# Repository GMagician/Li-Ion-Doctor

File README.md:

# Lithium battery doctor

**PROOF OF CONCEPT PROJECT**

**:warning::boom: WARNING:LITHIUM BATTERY MAY EASILY EXPLODE OR TAKE FIRE, REPLICATE THIS PROJECT AT YOUR OWN RISK:boom::warning:**

Complete solution for Li Ion batteries

Features:<br />
  Charge, discharge, amp hours count, test for short or open circuit, weak battery indicator, measure internal resistance.

- Charge:<br />
  TP4056 module (integrated), selectable current ~200/500/1000mA. TP4056 circuit is monitored by Arduino.
- Discharge:<br />
  current up to 2000mA (step 20mA), PWM controlled. Internal resistance is calculated from battery voltage drop under load.
- Capacity:<br />
  Battery gets fully charged, then discharged, mAh on selected current load is counted.
- Recovery:<br />
  Deep discharged battery charge with 100mA current.<br /><br />

This is a revisited project originally developped by Akos Boda in 2022 (https://www.thingiverse.com/thing:5229303).

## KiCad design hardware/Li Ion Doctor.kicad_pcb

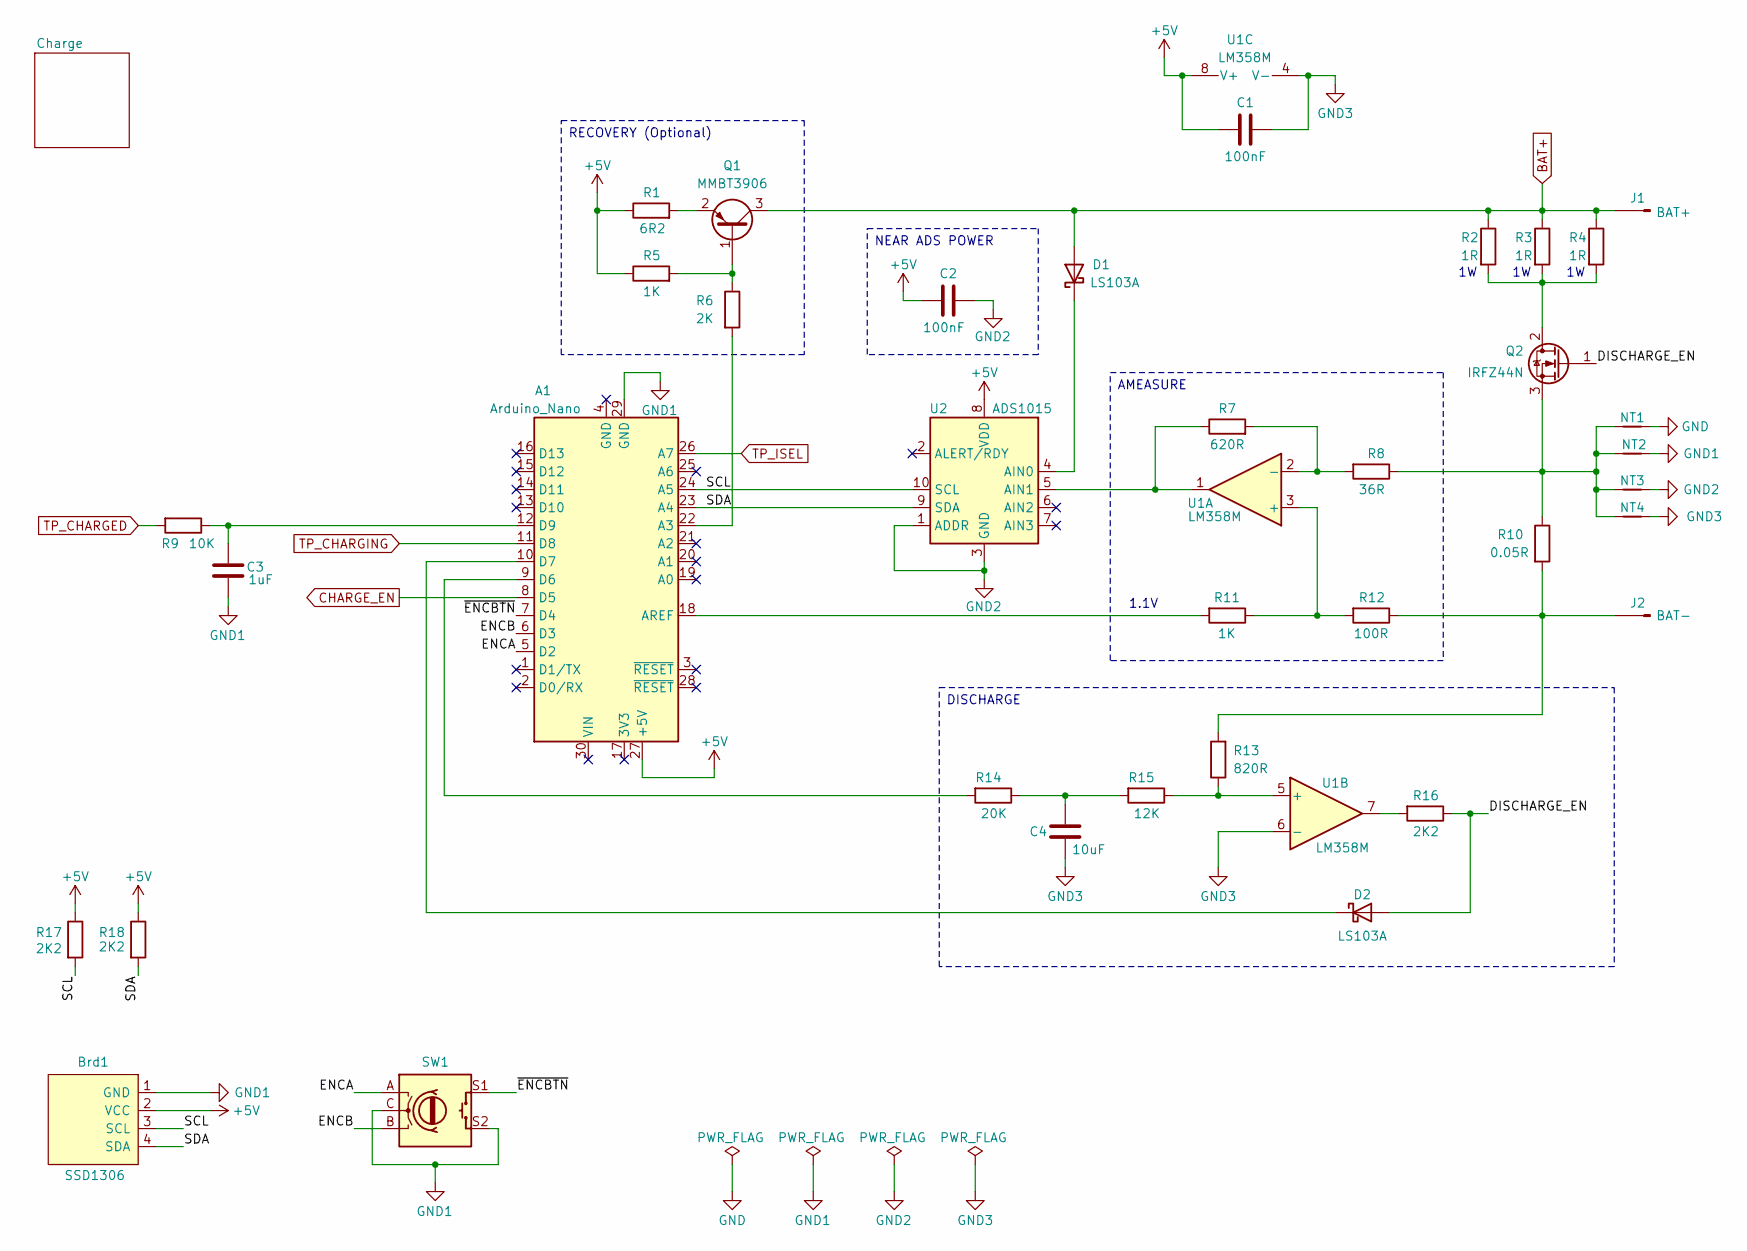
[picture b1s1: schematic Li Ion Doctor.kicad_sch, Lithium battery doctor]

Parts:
A1: Arduino_Nano
Brd1: SSD1306; SSD1306_OLED_DISPLAY_0.96
C1, C2: 100nF; C_0805_2012Metric_Pad1.18x1.45mm_HandSolder
C3: 1uF; C_0805_2012Metric_Pad1.18x1.45mm_HandSolder
C4: 10uF; C_0805_2012Metric_Pad1.18x1.45mm_HandSolder
D1, D2: LS103A; D_SOD-80
J1: BAT+; Pin_D1.0mm_L10.0mm_LooseFit
J2: BAT-; Pin_D1.0mm_L10.0mm_LooseFit
NT1: NetTie_2; NetTie-2_SMD_Pad2.0mm
NT2, NT3, NT4: NetTie_2; NetTie-2_SMD_Pad0.5mm
Q1: MMBT3906; SOT-23
Q2: IRFZ44N; TO-220-3_Vertical
R1: 6R2; R_0805_2012Metric_Pad1.20x1.40mm_HandSolder
R2, R3, R4: 1R; R_2512_6332Metric_Pad1.40x3.35mm_HandSolder
R5, R11: 1K; R_0805_2012Metric_Pad1.20x1.40mm_HandSolder
R6: 2K; R_0805_2012Metric_Pad1.20x1.40mm_HandSolder
R7: 620R; R_0805_2012Metric_Pad1.20x1.40mm_HandSolder
R8: 36R; R_0805_2012Metric_Pad1.20x1.40mm_HandSolder
R9: 10K; R_0805_2012Metric_Pad1.20x1.40mm_HandSolder
R10: 0.05R; R_Bare_Metal_Element_L18mm_W2.5mm_P15mm
R12: 100R; R_0805_2012Metric_Pad1.20x1.40mm_HandSolder
R13: 820R; R_0805_2012Metric_Pad1.20x1.40mm_HandSolder
R14: 20K; R_0805_2012Metric_Pad1.20x1.40mm_HandSolder
R15: 12K; R_0805_2012Metric_Pad1.20x1.40mm_HandSolder
R16, R17, R18: 2K2; R_0805_2012Metric_Pad1.20x1.40mm_HandSolder
SW1: RotaryEncoder_Switch; RotaryEncoder-Switch_Vertical_H15mm
U1: LM358M; SOP-8_3.9x4.9mm_P1.27mm
U2: ADS1015; TSSOP-10_3x3mm_P0.5mm

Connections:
+5V: A1.27 (+5V), Brd1.2 (VCC), C1.1, C2.1, R1.1, R5.1, R17.1, R18.1, U1.8 (V+), U2.8 (VDD); also elsewhere on the board
/DISCHARGE_EN: D2.2 (A), Q2.1 (G), R16.1
/ENCA: A1.5 (D2), SW1.A
/ENCB: A1.6 (D3), SW1.B
/SCL: A1.24 (A5), Brd1.3 (SCL), R17.2, U2.10 (SCL)
/SDA: A1.23 (A4), Brd1.4 (SDA), R18.2, U2.9 (SDA)
/~ENCBTN: A1.7 (D4), SW1.S1
BAT+: D1.2 (A), J1.1, Q1.3 (C), R2.1, R3.1, R4.1; also elsewhere on the board
CHARGE_EN: A1.8 (D5); also elsewhere on the board
GND: NT1.1; also elsewhere on the board
GND1: A1.29 (GND), Brd1.1 (GND), C3.1, NT2.1, SW1.C, SW1.S2; also elsewhere on the board
GND2: C2.2, NT3.1, U2.1 (ADDR), U2.3 (GND)
GND3: C1.2, C4.2, NT4.1, U1.4 (V-), U1.6 (-)
unnamed: A1.22 (A3), R6.2
unnamed: A1.18 (AREF), R11.2
unnamed: A1.9 (D6), R14.2
unnamed: A1.10 (D7), D2.1 (K)
unnamed: A1.12 (D9), C3.2, R9.1
unnamed: C4.1, R14.1, R15.2
unnamed: D1.1 (K), U2.4 (AIN0)
unnamed: J2.1, R10.2, R12.1, R13.2
unnamed: Q1.1 (B), R5.2, R6.1
unnamed: Q1.2 (E), R1.2
unnamed: Q2.2 (D), R2.2, R3.2, R4.2
unnamed: NT1.2, NT2.2, NT3.2, NT4.2, Q2.3 (S), R8.1, R10.1
unnamed: R16.2, U1.7
unnamed: R11.1, R12.2, U1.3 (+)
unnamed: R7.2, R8.2, U1.2 (-)
unnamed: R13.1, R15.1, U1.5 (+)
unnamed: R7.1, U1.1, U2.5 (AIN1)
TP_CHARGED: R9.2; also elsewhere on the board
TP_CHARGING: A1.11 (D8); also elsewhere on the board
TP_ISEL: A1.26 (A7); also elsewhere on the board

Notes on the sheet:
1.1V
DISCHARGE
RECOVERY (Optional)
NEAR ADS POWER
AMEASURE

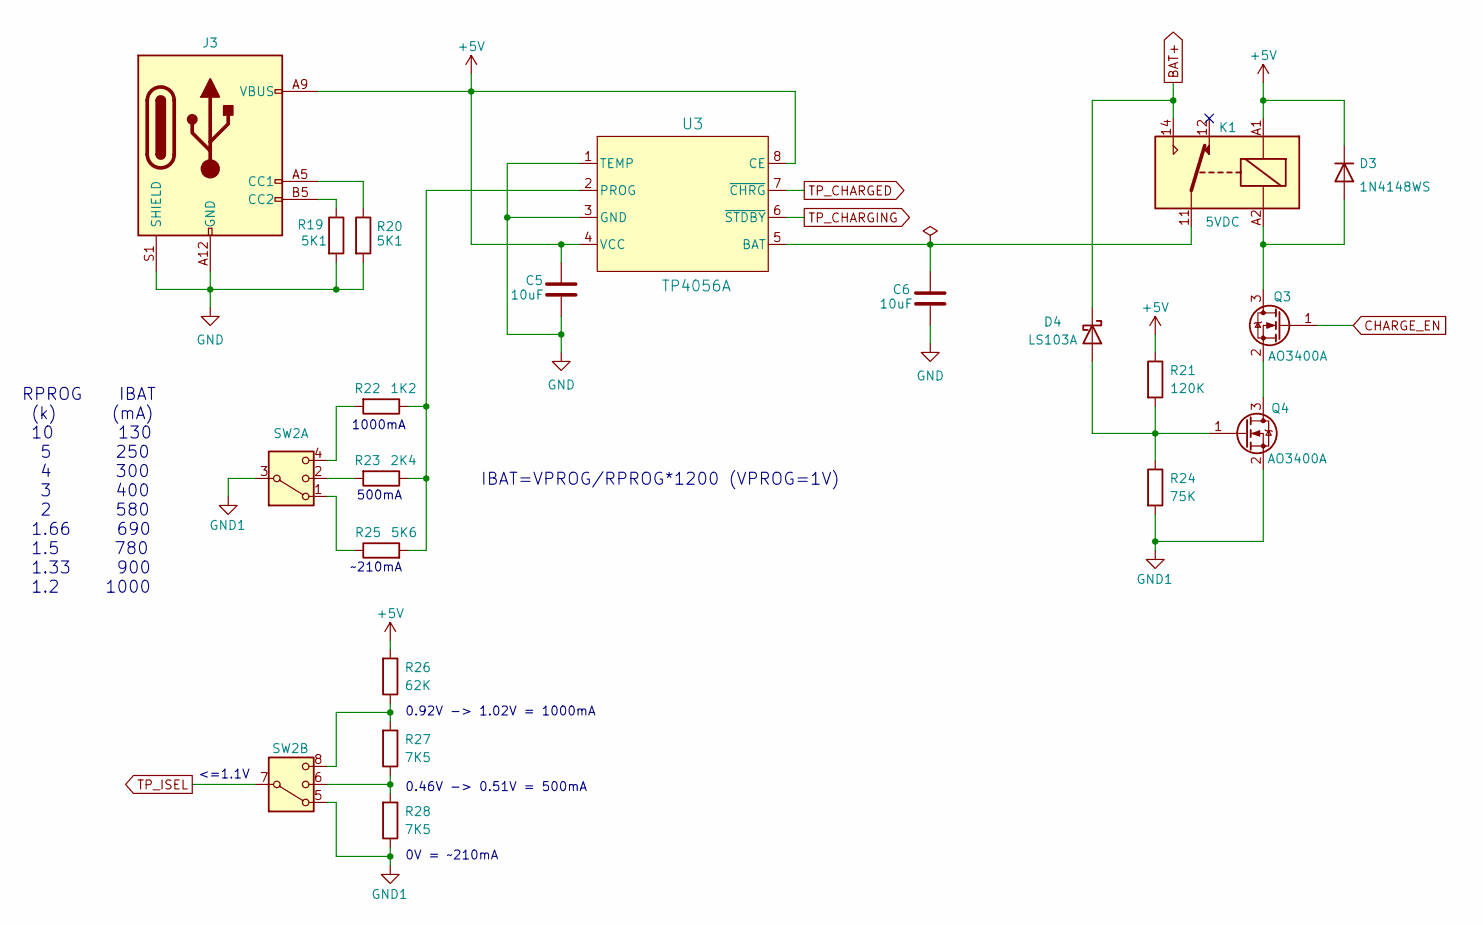
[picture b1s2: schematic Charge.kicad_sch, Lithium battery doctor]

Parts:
C5, C6: 10uF; C_0805_2012Metric_Pad1.18x1.45mm_HandSolder
D3: 1N4148WS; D_SOD-323_HandSoldering
D4: LS103A; D_SOD-80
J3: USB_C_Receptacle_PowerOnly_6P; USB_C_Receptacle_GCT_USB4125-xx-x_6P_TopMnt_Horizontal
K1: 5VDC; Relay_SPDT_Finder_36.11
Q3, Q4: AO3400A; SOT-23
R19, R20: 5K1; R_0805_2012Metric_Pad1.20x1.40mm_HandSolder
R21: 120K; R_0805_2012Metric_Pad1.20x1.40mm_HandSolder
R22: 1K2; R_0805_2012Metric_Pad1.20x1.40mm_HandSolder
R23: 2K4; R_0805_2012Metric_Pad1.20x1.40mm_HandSolder
R24: 75K; R_0805_2012Metric_Pad1.20x1.40mm_HandSolder
R25: 5K6; R_0805_2012Metric_Pad1.20x1.40mm_HandSolder
R26: 62K; R_0805_2012Metric_Pad1.20x1.40mm_HandSolder
R27, R28: 7K5; R_0805_2012Metric_Pad1.20x1.40mm_HandSolder
SW2: SW_DP3T; SK23D07VG5
U3: TP4056A; SOP-8_4.2x5.3mm_P1.27mm_EP2.5x3.4mm_ThermalVias

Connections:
+5V: C5.1, D3.1 (K), J3.A9 (VBUS), J3.B9 (VBUS), K1.A1, R21.1, R26.2, U3.4 (VCC), U3.8 (CE); also elsewhere on the board
BAT+: D4.1 (K), K1.14; also elsewhere on the board
CHARGE_EN: Q3.1 (G); also elsewhere on the board
GND: C5.2, C6.1, J3.A12 (GND), J3.B12 (GND), J3.S1 (SHIELD), R19.2, R20.2, U3.1 (TEMP), U3.3 (GND), U3.9 (GND); also elsewhere on the board
GND1: Q4.2 (S), R24.2, R28.1, SW2.3, SW2.5; also elsewhere on the board
unnamed: D3.2 (A), K1.A2, Q3.3 (D)
unnamed: D4.2 (A), Q4.1 (G), R21.2, R24.1
unnamed: J3.A5 (CC1), R20.1
unnamed: J3.B5 (CC2), R19.1
unnamed: Q3.2 (S), Q4.3 (D)
unnamed: R22.2, SW2.4
unnamed: R23.2, SW2.2
unnamed: R25.1, SW2.1
unnamed: R26.1, R27.2, SW2.8
unnamed: R27.1, R28.2, SW2.6
unnamed: C6.2, K1.11, U3.5 (BAT)
unnamed: R22.1, R23.1, R25.2, U3.2 (PROG)
TP_CHARGED: U3.7 (~CHRG); also elsewhere on the board
TP_CHARGING: U3.6 (~STDBY); also elsewhere on the board
TP_ISEL: SW2.7; also elsewhere on the board

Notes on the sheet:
IBAT=VPROG/RPROG*1200 (VPROG=1V)
<=1.1V
500mA
RPROG IBAT (k) (mA) 10 130 5 250 4 300 3 400 2 580 1.66 690 1.5 780 1.33 900 1.2 1000
0.46V -> 0.51V = 500mA
0.92V -> 1.02V = 1000mA
~210mA
0V = ~210mA
1000mA

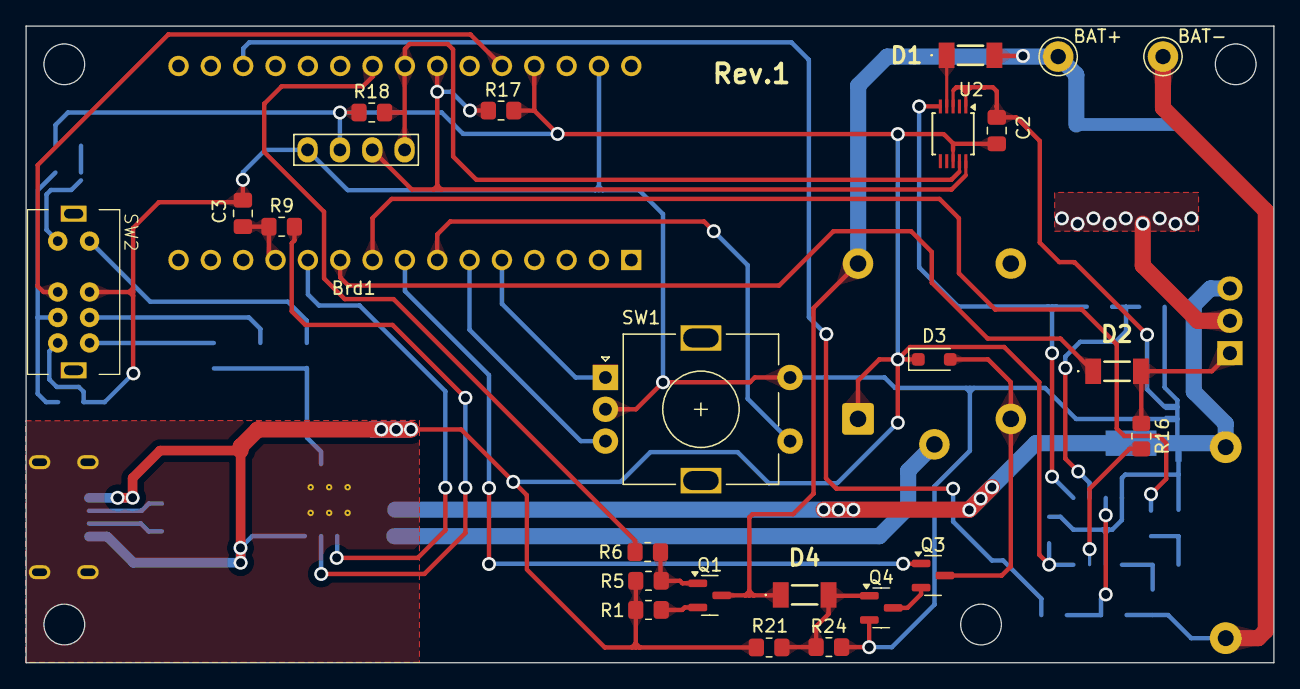
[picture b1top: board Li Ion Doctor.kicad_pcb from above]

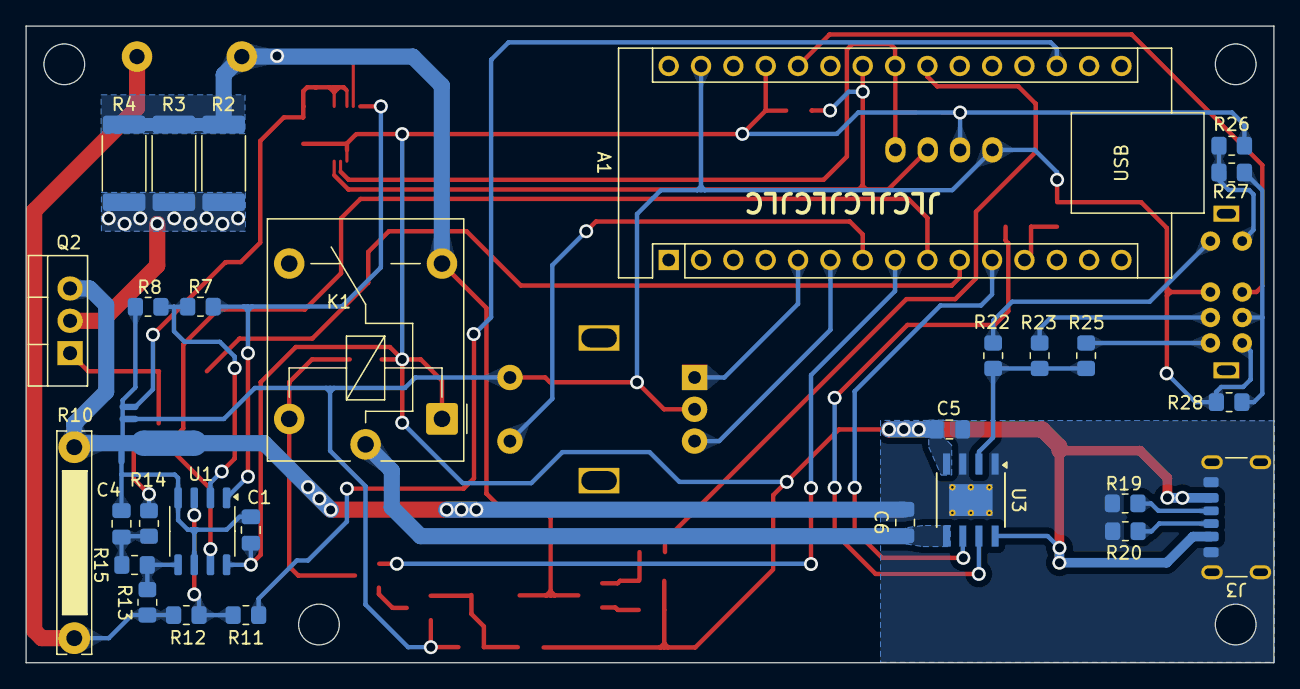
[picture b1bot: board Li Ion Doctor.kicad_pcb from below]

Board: 2 copper layers, 98.0 x 50.0 mm, 57 parts (33 on the bottom side), 45 nets.

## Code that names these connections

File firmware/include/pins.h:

#pragma once

// 0/RX
// 1/TX
#define ENCA_PIN                  2
#define ENCB_PIN                  3
#define ENCBTN_PIN                4
#define CHARGE_EN_PIN             5
#define DISCHARGE_PWM_PIN         6
#define DISCHARGE_EN_PIN          7
#define TP_CHARGING_PIN           8
#define TP_CHARGED_PIN            9
// 10
// 11
// 12
// 13
// A0
// A1
// A2
#define RECOVERY_DIS_PIN          A3
// SDA                            A4
// SCL                            A5
// A6
#define TP_ISEL_PIN               A7

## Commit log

2025-05-01 Remove some warnings
